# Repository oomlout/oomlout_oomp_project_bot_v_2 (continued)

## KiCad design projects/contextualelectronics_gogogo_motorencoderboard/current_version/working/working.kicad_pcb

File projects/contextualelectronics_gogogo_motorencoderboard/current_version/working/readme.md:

# gogogo
 
## summary 
* id: contextualelectronics_gogogo_motorencoderboard
* user: contextualelectronics
* name: gogogo
* board: motorencoderboard
* repo: https://github.com/ContextualElectronics/GoGoGo
* src_file_repo_kicad_pcb: MotorEncoderBoard/MotorEncoderBoard.kicad_pcb
* src_file_repo_kicad_pcb_link: https://github.com/ContextualElectronics/GoGoGo/tree/master/MotorEncoderBoard/MotorEncoderBoard.kicad_pcb

* src_file_repo_sch: MotorEncoderBoard/MotorEncoderBoard.sch
* src_file_repo_sch_link: https://github.com/ContextualElectronics/GoGoGo/tree/master/MotorEncoderBoard/MotorEncoderBoard.sch
* full details link: https://github.com/oomlout/oomlout_oomp_project_bot_v_2/tree/main/projects/contextualelectronics_gogogo_motorencoderboard/current_version/working  

## schematic  
  
[schematic (pdf)](working_schematic.pdf) 

## pcb  

[board (pdf)](working.pdf)  

## working_bom
| Id | Designator | Footprint | Quantity | Designation | Supplier and ref |  | None | 
| --- | --- | --- | --- | --- | --- | --- | --- | 
| 1 | C1 | C_0805_HandSoldering | 1 | C |  |  | [''] | 
| 2 | P1,P2 | Pin_Header_Straight_1x02 | 2 | CONN_01X02 |  |  | [''] | 
| 3 | R1 | R_0805_HandSoldering | 1 | 100 |  |  | [''] | 
| 4 | R2,R3,R4,R5 | R_0805_HandSoldering | 4 | 1K |  |  | [''] | 
| 5 | TP1 | Measurement_Point_Round-SMD-Pad_Small | 1 | OptoOut |  |  | [''] | 
| 6 | U2 | SOIC-8_3.9x4.9mm_Pitch1.27mm | 1 | LM311N |  |  | [''] | 
| 7 | U1 | RPI-579N1 | 1 | RPI-579N1 |  |  | [''] | 

## bom_schematic
| Ref | Qnty | Value | Cmp name | Footprint | Description | Vendor | DNP | 
| --- | --- | --- | --- | --- | --- | --- | --- | 
| C1 | 1 | C | C | Capacitors_SMD:C_0805_HandSoldering |  |  |  | 
| P1, P2 | 2 | CONN_01X02 | CONN_01X02 | Pin_Headers:Pin_Header_Straight_1x02 |  |  |  | 
| R1 | 1 | 100 | R | Resistors_SMD:R_0805_HandSoldering |  |  |  | 
| R2, R3, R4, R5 | 4 | 1K | R | Resistors_SMD:R_0805_HandSoldering |  |  |  | 
| TP1 | 1 | OptoOut | CONN_01X01 | Measurement_Points:Measurement_Point_Round-SMD-Pad_Big |  |  |  | 
| U1 | 1 | RPI-579N1 | RPI-579N1 | MotorEncoder:RPI-579N1 | LTV-817, DIP-4, DC Optocoupler, Vce 35V, CTR 50% |  |  | 
| U2 | 1 | LM311DR | LM311N | Housings_SOIC:SOIC-8_3.9x4.9mm_Pitch1.27mm |  |  |  |

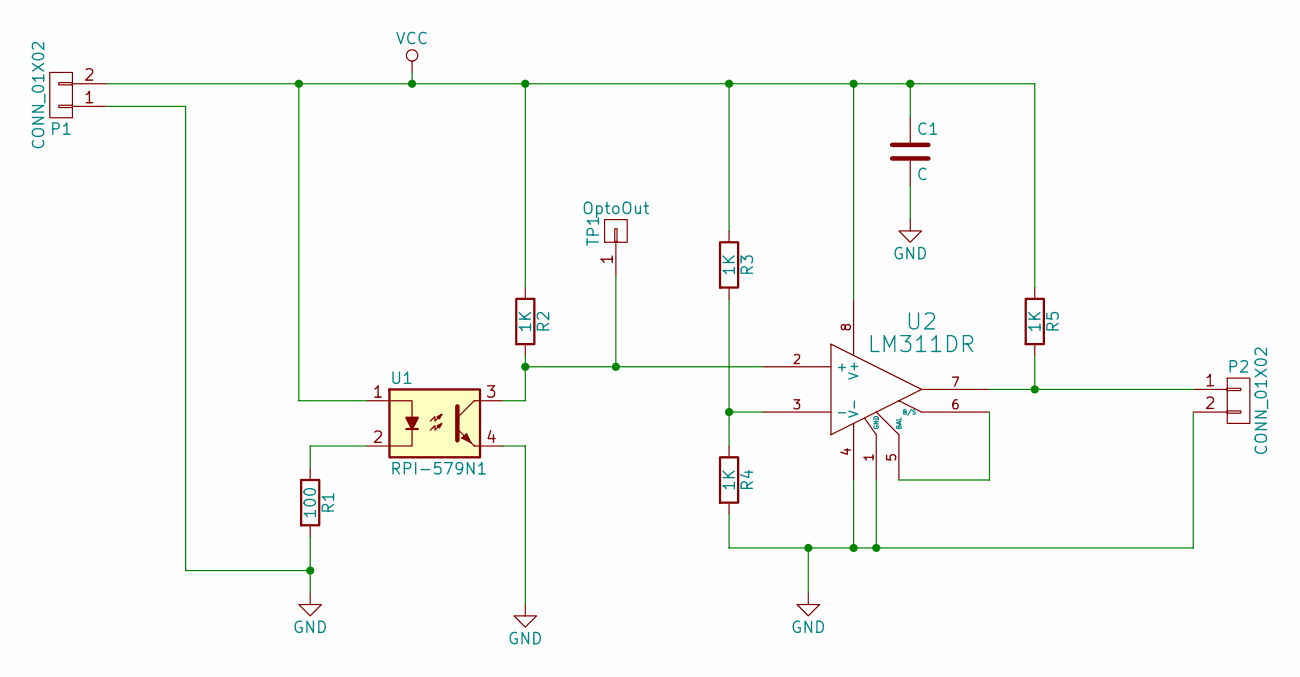
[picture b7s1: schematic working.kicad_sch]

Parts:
C1: C; C_0805_HandSoldering
P1, P2: CONN_01X02; Pin_Header_Straight_1x02
R1: 100; R_0805_HandSoldering
R2, R3, R4, R5: 1K; R_0805_HandSoldering
TP1: OptoOut; Measurement_Point_Round-SMD-Pad_Big
U1: RPI-579N1; MPN RPI-579N1
U2: LM311DR; SOIC-8_3.9x4.9mm_Pitch1.27mm; MPN LM311DR

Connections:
GND: C1.2, P1.1, P2.2, R1.2, R4.2, U1.4, U2.1 (GND), U2.4 (V-)
unnamed: P2.1, R5.2, U2.7
unnamed: R1.1, U1.2
unnamed: R2.2, TP1.1, U1.3, U2.2 (+)
unnamed: R3.2, R4.1, U2.3 (-)
unnamed: U2.5 (BAL), U2.6 (B/S)
VCC: C1.1, P1.2, R2.1, R3.1, R5.1, U1.1, U2.8 (V+)

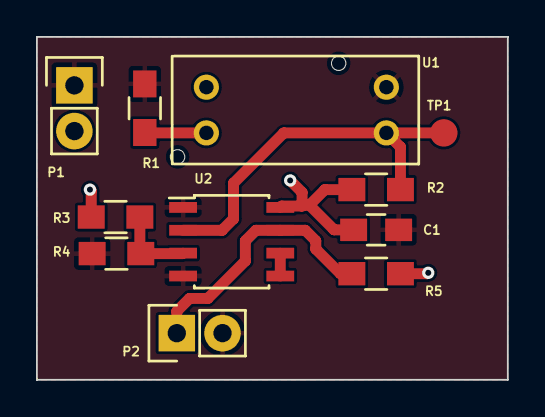
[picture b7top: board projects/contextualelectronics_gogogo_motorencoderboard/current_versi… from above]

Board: 2 copper layers, 26.2 x 19.0 mm, 11 parts (0 on the bottom side), 7 nets.
